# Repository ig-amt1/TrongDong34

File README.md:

# TrongDong34
A ferris shape keyboard using XIAO controller, this is my attempt to create a cheap BLE ferris alike. Unfortunately because of the lack of pin on the Xiao controller, this have to use diode.

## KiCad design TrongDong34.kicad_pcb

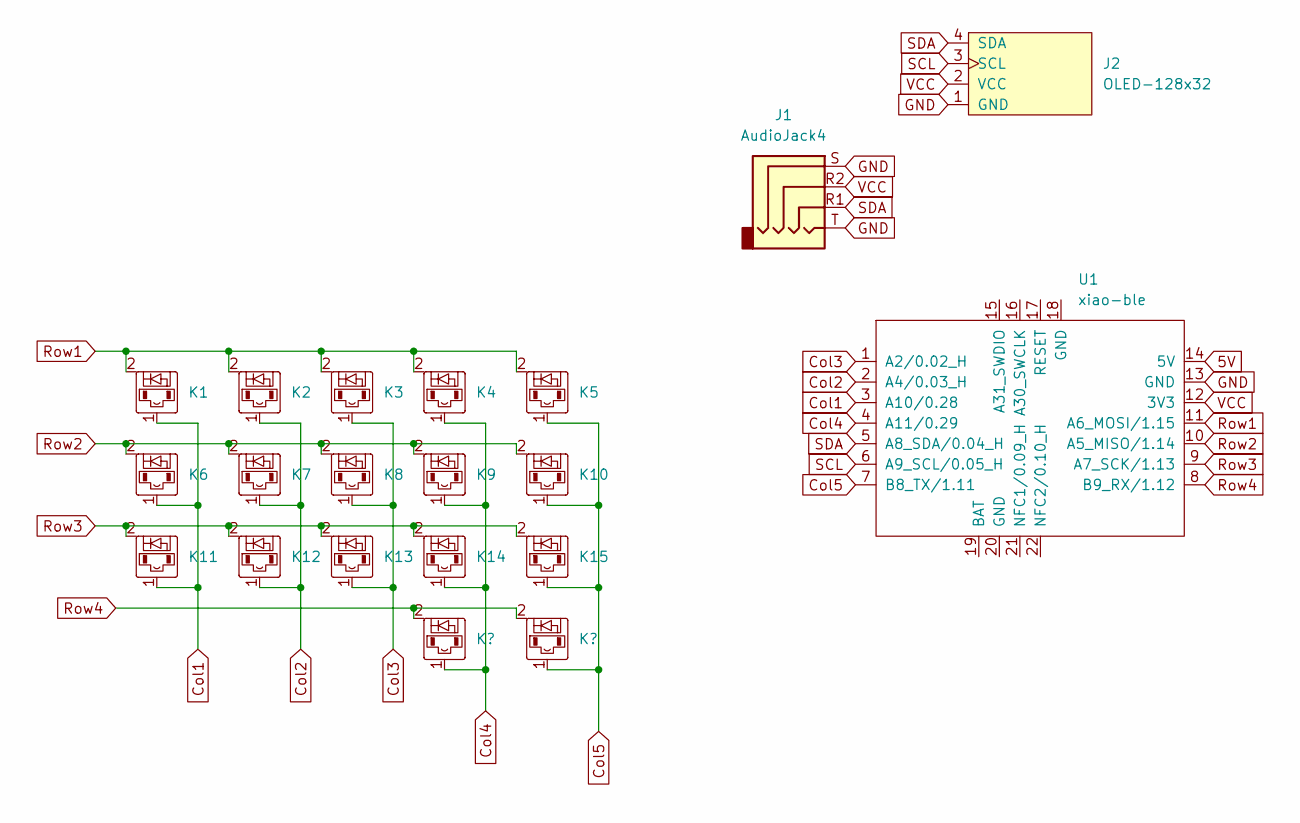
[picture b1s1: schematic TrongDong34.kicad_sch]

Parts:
J1: AudioJack4; PJ-320A
J2: OLED-128x32; OLED-128x32-cutout
K1, K2, K3, K4, K5, K6, K7, K8, K9, K10, K11, K12, K13, K14, K15: diode-choc; pg1350-DR
U1: xiao-ble; xiao-ble-tht

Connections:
5V: U1.14 (5V)
Col1: K1.1, K6.1, K11.1, U1.3 (A10/0.28)
Col2: K2.1, K7.1, K12.1, U1.2 (A4/0.03_H)
Col3: K3.1, K8.1, K13.1, U1.1 (A2/0.02_H)
Col4: K4.1, K9.1, K14.1, U1.4 (A11/0.29); also elsewhere on the board
Col5: K5.1, K10.1, K15.1, U1.7 (B8_TX/1.11); also elsewhere on the board
GND: J1.S, J1.T, J2.1 (GND), U1.13 (GND)
Row1: K1.2, K2.2, K3.2, K4.2, K5.2, U1.11 (A6_MOSI/1.15)
Row2: K6.2, K7.2, K8.2, K9.2, K10.2, U1.10 (A5_MISO/1.14)
Row3: K11.2, K12.2, K13.2, K14.2, K15.2, U1.9 (A7_SCK/1.13)
Row4: U1.8 (B9_RX/1.12); also elsewhere on the board
SCL: J2.3 (SCL), U1.6 (A9_SCL/0.05_H)
SDA: J1.R1, J2.4 (SDA), U1.5 (A8_SDA/0.04_H)
VCC: J1.R2, J2.2 (VCC), U1.12 (3V3)

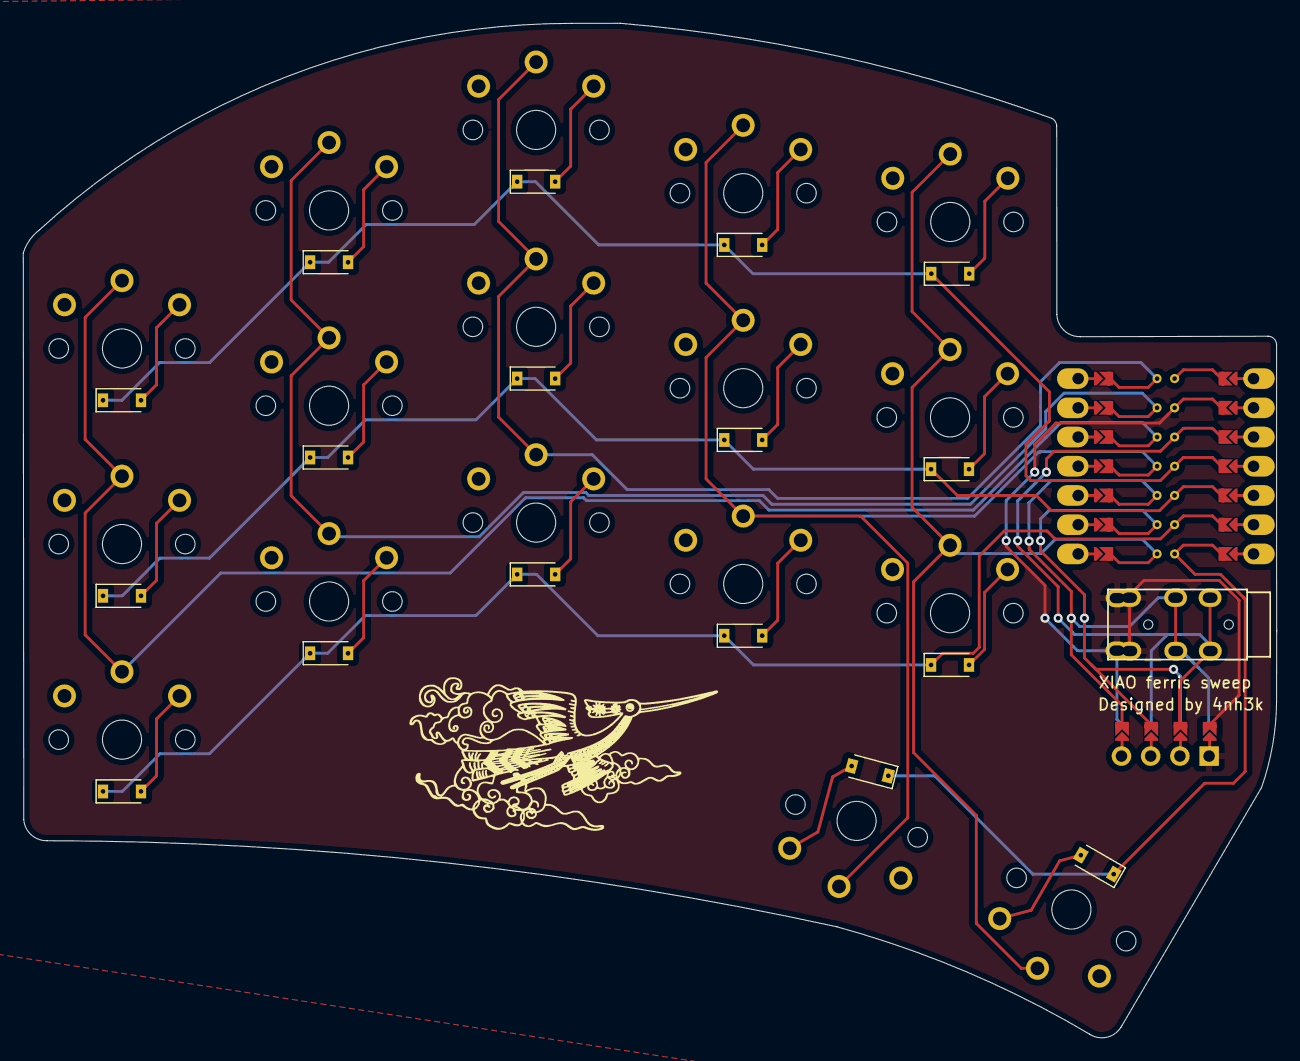
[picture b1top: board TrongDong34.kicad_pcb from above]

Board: 2 copper layers, 109.0 x 88.2 mm, 20 parts (0 on the bottom side), 13 nets.

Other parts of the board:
K16, K17: diode-choc; pg1350-DR

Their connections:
Col4: K16.1; also elsewhere on the board
Col5: K17.1; also elsewhere on the board
Row4: K16.2, K17.2; also elsewhere on the board

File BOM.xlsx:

Designator | MPN/Seeed SKU | Qty | Link
U1 | 102010448 | 1 | https://statics3.seeedstudio.com/fusion/opl/datasheet/102010448.pdf
K1,K2,K3,K4,K5,K6,K7,K8,K9,K10,K11,K12,K13,K14,K15,K16,K17 | 304010007 | 17 | https://statics3.seeedstudio.com/fusion/opl/datasheet/304010007.pdf

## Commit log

2022-09-10 add kicad project
